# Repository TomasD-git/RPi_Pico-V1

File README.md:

# RPi_Pico-V1  

## Description  
**Normal RPi pico with 16Mb/128Mbit of flash (which is 8x more than clasic rpi pico)**  

- Supports any firmware compatible with rpi pico, just make sure to select 16mb flash to use full storage.    

**i made this project because RPi picos dont have usb-c port and have less storage**  

###### BOM is at the very bottom  
###### lcsc BOM is in production folder  

## Pictures  

**Schematic**  

**PCB**  

**3D viewer (Top view)**  

**3D viewer (Bottom view)**  

<details>
<summary>BOM</summary>

| Name | Purpose | Quantity | Total Cost (USD) | Link | Distributor |
| ---- | ------- | -------- | ---------------- | ---- | ----------- |
| PCB + stencil | all components are on this | 1 | 34.95 | https://jlcpcb.com | jlcpcb |
|ALL components | all components that are on pcb | 1 | 35.54 | https://lcsc.com | lcsc |
|               |                   | Total cost | 70.49 |  |  |

</details>

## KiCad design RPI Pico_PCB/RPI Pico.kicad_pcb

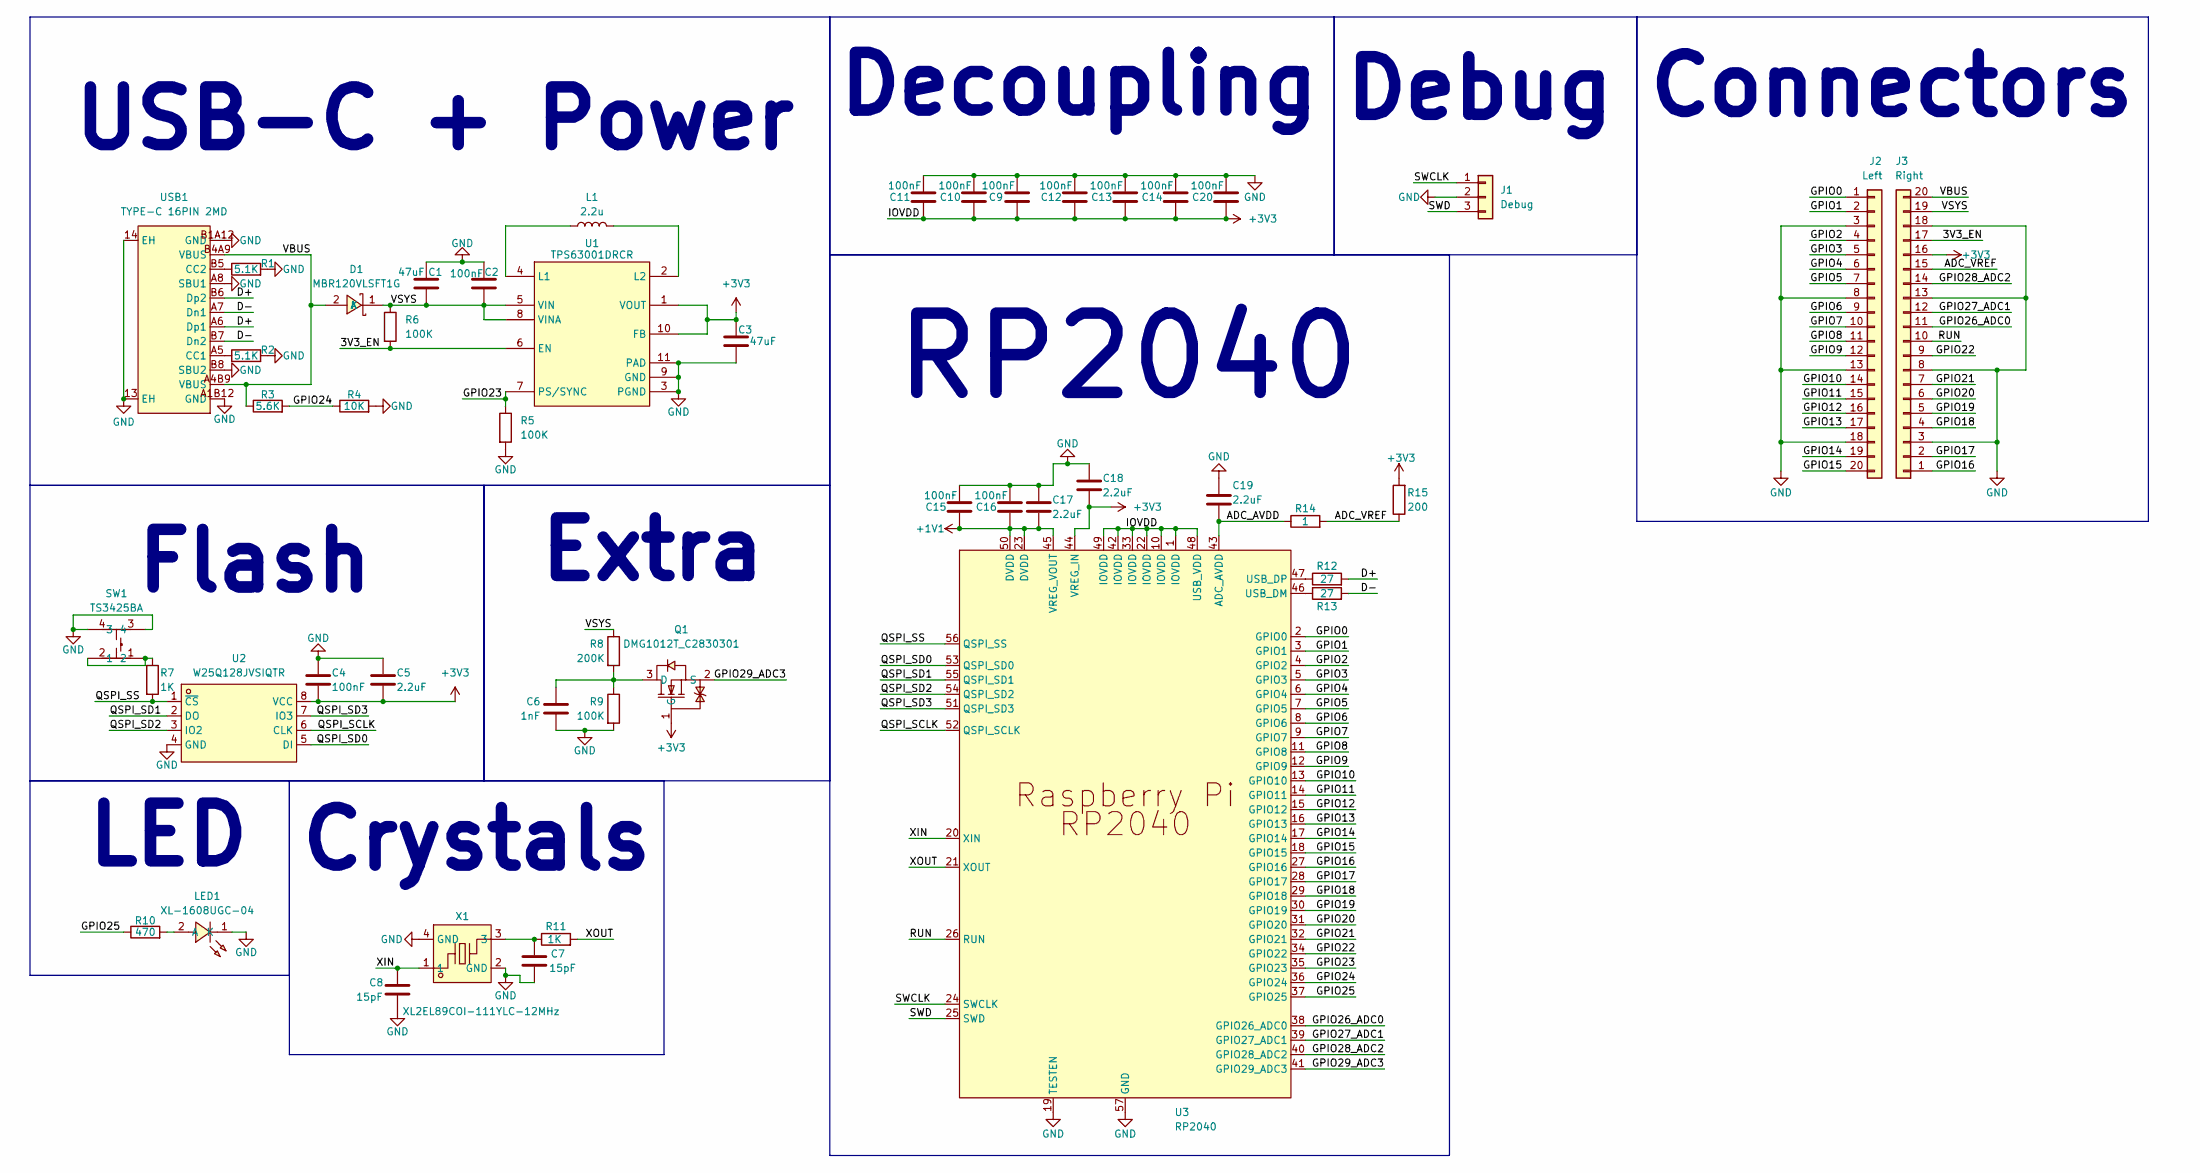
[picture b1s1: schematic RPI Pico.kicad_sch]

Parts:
C1, C3: 47uF; C_1206_3216Metric
C2, C4, C9, C10, C11, C12, C13, C14, C15, C16, C20: 100nF; C_0603_1608Metric
C5, C17, C18, C19: 2.2uF; C_0805_2012Metric
C6: 1nF; C_0402_1005Metric
C7, C8: 15pF; C_0402_1005Metric
D1: MBR120VLSFT1G; SOD-123F_L2.8-W1.8-LS3.7-RD; MPN MBR120VLSFT1G; LCSC Part C223608
J1: Debug
J2: Left
J3: Right
L1: 2.2u; L_1008_2520Metric
LED1: XL-1608UGC-04; LED0603-RD_GREEN; MPN XL-1608UGC-04; LCSC Part C965804
Q1: DMG1012T_C2830301; SOT-523-3_L1.6-W0.8-P1.00-LS1.6-BR; MPN DMG1012T; LCSC Part C2830301
R1, R2: 5.1K; R_0603_1608Metric
R3: 5.6K; R_0603_1608Metric
R4: 10K; R_0603_1608Metric
R5, R6, R9: 100K; R_0603_1608Metric
R7, R11: 1K; R_0603_1608Metric
R8: 200K; R_0805_2012Metric
R10: 470; R_0603_1608Metric
R12, R13: 27; R_0603_1608Metric
R14: 1; R_0402_1005Metric
R15: 200; R_0603_1608Metric
SW1: TS3425BA; SW-SMD_4P-L4.2-W3.2-P2.15-LS4.6-1; MPN TS3425BA; LCSC Part C2681476
U1: TPS63001DRCR; VSON-10_L3.0-W3.0-P0.50-TL-EP_TPS62410DRCR; MPN TPS63001DRCR; LCSC Part C28060
U2: W25Q128JVSIQTR; SOIC-8_L5.3-W5.3-P1.27-LS8.0-BL; MPN W25Q128JVSIQ; LCSC Part C97521
U3: RP2040; LQFN-56_L7.0-W7.0-P0.4-EP; MPN RP2040; LCSC Part C2040
USB1: TYPE-C 16PIN 2MD; USB-C-SMD_TYPE-C-16PIN-2MD-073; MPN TYPE-C 16PIN 2MD(073); LCSC Part C2765186
X1: XL2EL89COI-111YLC-12MHz; CRYSTAL-SMD_4P-L3.2-W2.5-BL-1; MPN XL2EL89COI-111YLC-12M; LCSC Part C5280578

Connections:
+1V1: C15.2, C16.2, C17.2, U3.23 (DVDD), U3.45 (VREG_VOUT), U3.50 (DVDD)
+3V3: C3.1, C4.2, C5.2, C9.2, C10.2, C11.2, C12.2, C13.2, C14.2, C18.2, C20.2, J3.16, Q1.1 (G), R15.2, U1.1 (VOUT), U1.10 (FB), U2.8 (VCC), U3.1 (IOVDD), U3.10 (IOVDD), U3.22 (IOVDD), U3.33 (IOVDD), U3.42 (IOVDD), U3.44 (VREG_IN), U3.48 (USB_VDD), U3.49 (IOVDD)
/3V3_EN: J3.17, R6.2, U1.6 (EN)
/ADC_AVDD: C19.2, R14.1, U3.43 (ADC_AVDD)
/ADC_VREF: J3.15, R14.2, R15.1
/D+: R12.2, USB1.A6 (Dp1), USB1.B6 (Dp2)
/D-: R13.2, USB1.A7 (Dn1), USB1.B7 (Dn2)
/GPIO0: J2.1, U3.2 (GPIO0)
/GPIO1: J2.2, U3.3 (GPIO1)
/GPIO2: J2.4, U3.4 (GPIO2)
/GPIO3: J2.5, U3.5 (GPIO3)
/GPIO4: J2.6, U3.6 (GPIO4)
/GPIO5: J2.7, U3.7 (GPIO5)
/GPIO6: J2.9, U3.8 (GPIO6)
/GPIO7: J2.10, U3.9 (GPIO7)
/GPIO8: J2.11, U3.11 (GPIO8)
/GPIO9: J2.12, U3.12 (GPIO9)
/GPIO10: J2.14, U3.13 (GPIO10)
/GPIO11: J2.15, U3.14 (GPIO11)
/GPIO12: J2.16, U3.15 (GPIO12)
/GPIO13: J2.17, U3.16 (GPIO13)
/GPIO14: J2.19, U3.17 (GPIO14)
/GPIO15: J2.20, U3.18 (GPIO15)
/GPIO16: J3.1, U3.27 (GPIO16)
/GPIO17: J3.2, U3.28 (GPIO17)
/GPIO18: J3.4, U3.29 (GPIO18)
/GPIO19: J3.5, U3.30 (GPIO19)
/GPIO20: J3.6, U3.31 (GPIO20)
/GPIO21: J3.7, U3.32 (GPIO21)
/GPIO22: J3.9, U3.34 (GPIO22)
/GPIO23: R5.1, U1.7 (PS/SYNC), U3.35 (GPIO23)
/GPIO24: R3.2, R4.1, U3.36 (GPIO24)
/GPIO25: R10.1, U3.37 (GPIO25)
/GPIO26_ADC0: J3.11, U3.38 (GPIO26_ADC0)
/GPIO27_ADC1: J3.12, U3.39 (GPIO27_ADC1)
/GPIO28_ADC2: J3.14, U3.40 (GPIO28_ADC2)
/GPIO29_ADC3: Q1.2 (S), U3.41 (GPIO29_ADC3)
/QSPI_SCLK: U2.6 (CLK), U3.52 (QSPI_SCLK)
/QSPI_SD0: U2.5 (DI), U3.53 (QSPI_SD0)
/QSPI_SD1: U2.2 (DO), U3.55 (QSPI_SD1)
/QSPI_SD2: U2.3 (IO2), U3.54 (QSPI_SD2)
/QSPI_SD3: U2.7 (IO3), U3.51 (QSPI_SD3)
/QSPI_SS: R7.2, U2.1 (~CS), U3.56 (QSPI_SS)
/RUN: J3.10, U3.26 (RUN)
/SWCLK: J1.1, U3.24 (SWCLK)
/SWD: J1.3, U3.25 (SWD)
/VBUS: D1.2 (A), J3.20, R3.1, USB1.A4B9 (VBUS), USB1.B4A9 (VBUS)
/VSYS: C1.2, C2.2, D1.1 (K), J3.19, R6.1, R8.1, U1.5 (VIN), U1.8 (VINA)
/XIN: C8.1, U3.20 (XIN), X1.1
/XOUT: R11.2, U3.21 (XOUT)
GND: C1.1, C2.1, C3.2, C4.1, C5.1, C6.1, C7.2, C8.2, C9.1, C10.1, C11.1, C12.1, C13.1, C14.1, C15.1, C16.1, C17.1, C18.1, C19.1, C20.1, J1.2, J2.3, J2.8, J2.13, J2.18, J3.3, J3.8, J3.13, J3.18, LED1.1 (K), R1.2, R2.2, R4.2, R5.2, R9.2, SW1.3, SW1.4, U1.3 (PGND), U1.9 (GND), U1.11 (PAD), U2.4 (GND), U3.19 (TESTEN), U3.57 (GND), USB1.13 (EH), USB1.14 (EH), USB1.A1B12 (GND), USB1.A8 (SBU1), USB1.B1A12 (GND), USB1.B8 (SBU2), X1.2 (GND), X1.4 (GND)
unnamed: C7.1, R11.1, X1.3
unnamed: LED1.2 (A), R10.2
unnamed: C6.2, Q1.3 (D), R8.2, R9.1
unnamed: R7.1, SW1.1, SW1.2
unnamed: L1.1, U1.4 (L1)
unnamed: L1.2, U1.2 (L2)
unnamed: R13.1, U3.46 (USB_DM)
unnamed: R12.1, U3.47 (USB_DP)
unnamed: R2.1, USB1.A5 (CC1)
unnamed: R1.1, USB1.B5 (CC2)

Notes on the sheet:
LED
USB-C + Power
Flash
RP2040
Extra
Connectors
Decoupling
Debug
Crystals

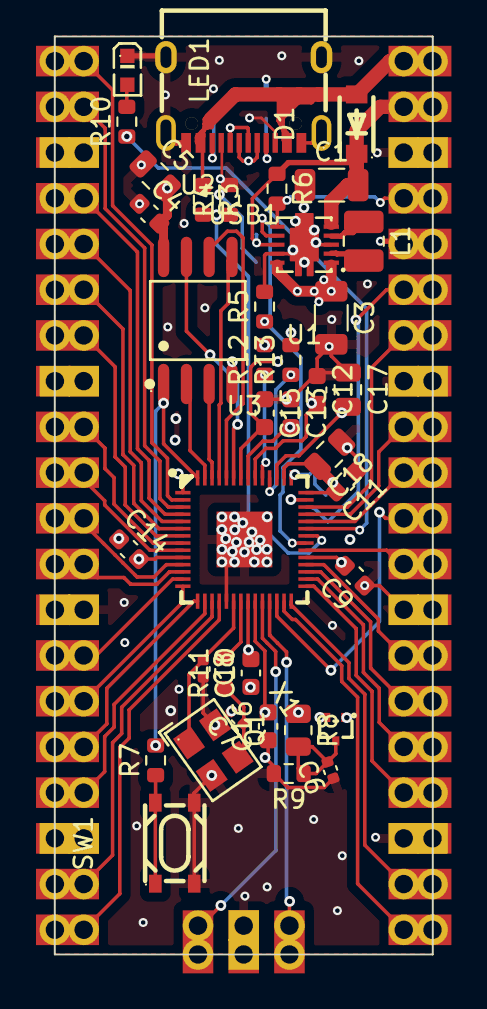
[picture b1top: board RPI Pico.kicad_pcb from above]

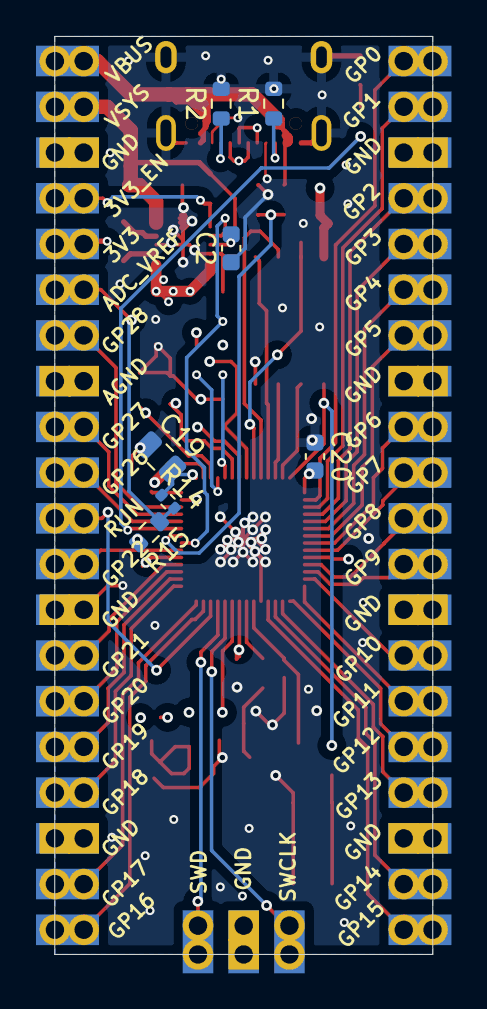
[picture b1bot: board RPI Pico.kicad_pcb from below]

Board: 4 copper layers, 21.0 x 51.0 mm, 45 parts (7 on the bottom side), 32 nets.

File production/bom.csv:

Designator,Footprint,Quantity,Value,LCSC Part #
"_86, _85, _84, _83, _82, _81, _80, _79, _78, _77, _76, _75, _74, _73, _72, _71, _70, _69, _68, _67, _66, _65, _64, _63, _62, _61, _60, _59, _58, _57, _56, _55, _54, _53, _52, _51, _50, _49, _48, _47, _46, _45, _44, _43, _42, _41, _40, _39, _38, _37, _36, _35, _34, _33, _32, _31, _30, _29, _28, _27, _26, _25, _24, _23, _22, _21, _20, _19, _18, _17, _16, _15, _14, _13, _12, _11, _10, _9, _8, _7, _6, _5, _4, _3, _2, ",,86,,
"C1, C3",1206,2,47uF,
"C10, C11, C12, C13, C14, C15, C16, C2, C20, C4, C9",0603,11,100nF,
"C17, C18, C19, C5",0805,4,2.2uF,
C6,0402,1,1nF,
"C7, C8",0402,2,15pF,
D1,SOD-123F_L2.8-W1.8-LS3.7-RD,1,MBR120VLSFT1G,C223608
L1,1008,1,2.2u,
LED1,LED0603-RD_GREEN,1,XL-1608UGC-04,C965804
Q1,SOT-523-3_L1.6-W0.8-P1.00-LS1.6-BR,1,DMG1012T_C2830301,C2830301
"R1, R2",0603,2,5.1K,
R10,0603,1,470,
"R11, R7",0603,2,1K,
"R12, R13",0603,2,27,
R14,0402,1,1,
R15,0603,1,200,
R3,0603,1,5.6K,
R4,0603,1,10K,
"R5, R6, R9",0603,3,100K,
R8,0805,1,200K,
SW1,SW-SMD_4P-L4.2-W3.2-P2.15-LS4.6-1,1,TS3425BA,C2681476
U1,VSON-10_L3.0-W3.0-P0.50-TL-EP_TPS62410DRCR,1,TPS63001DRCR,C28060
U2,SOIC-8_L5.3-W5.3-P1.27-LS8.0-BL,1,W25Q128JVSIQTR,C97521
U3,LQFN-56_L7.0-W7.0-P0.4-EP,1,RP2040,C2040
USB1,USB-C-SMD_TYPE-C-16PIN-2MD-073,1,TYPE-C 16PIN 2MD,C2765186
X1,CRYSTAL-SMD_4P-L3.2-W2.5-BL-1,1,XL2EL89COI-111YLC-12MHz,C5280578

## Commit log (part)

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2026-06-19 added BOM
2026-06-19 added kicad files
2026-06-19 added updated lcsc bom
